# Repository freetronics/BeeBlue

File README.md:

Freetronics Bluetooth Module for XBee
=====================================
Copyright 2014 Freetronics Pty Ltd <http://www.freetronics.com.au>  

A Bluetooth module with an XBee footprint, so that it can be inserted
into boards designed to use XBee modules and give them Bluetooth
capability instead.

More information is available at:

  http://www.freetronics.com.au/beeblue

INSTALLATION
------------
The design is saved as an EAGLE project. EAGLE PCB design software is
available from www.cadsoftusa.com free for non-commercial use. To use
this project download it and place the directory containing these files
into the "eagle" directory on your computer. Then open EAGLE and
navigate to the project.

DISTRIBUTION
------------
The specific terms of distribution of this project are governed by the
license referenced below.

LICENSE
-------
Licensed under the TAPR Open Hardware License (www.tapr.org/OHL).
The "license" folder within this repository also contains a copy of
this license in plain text format.

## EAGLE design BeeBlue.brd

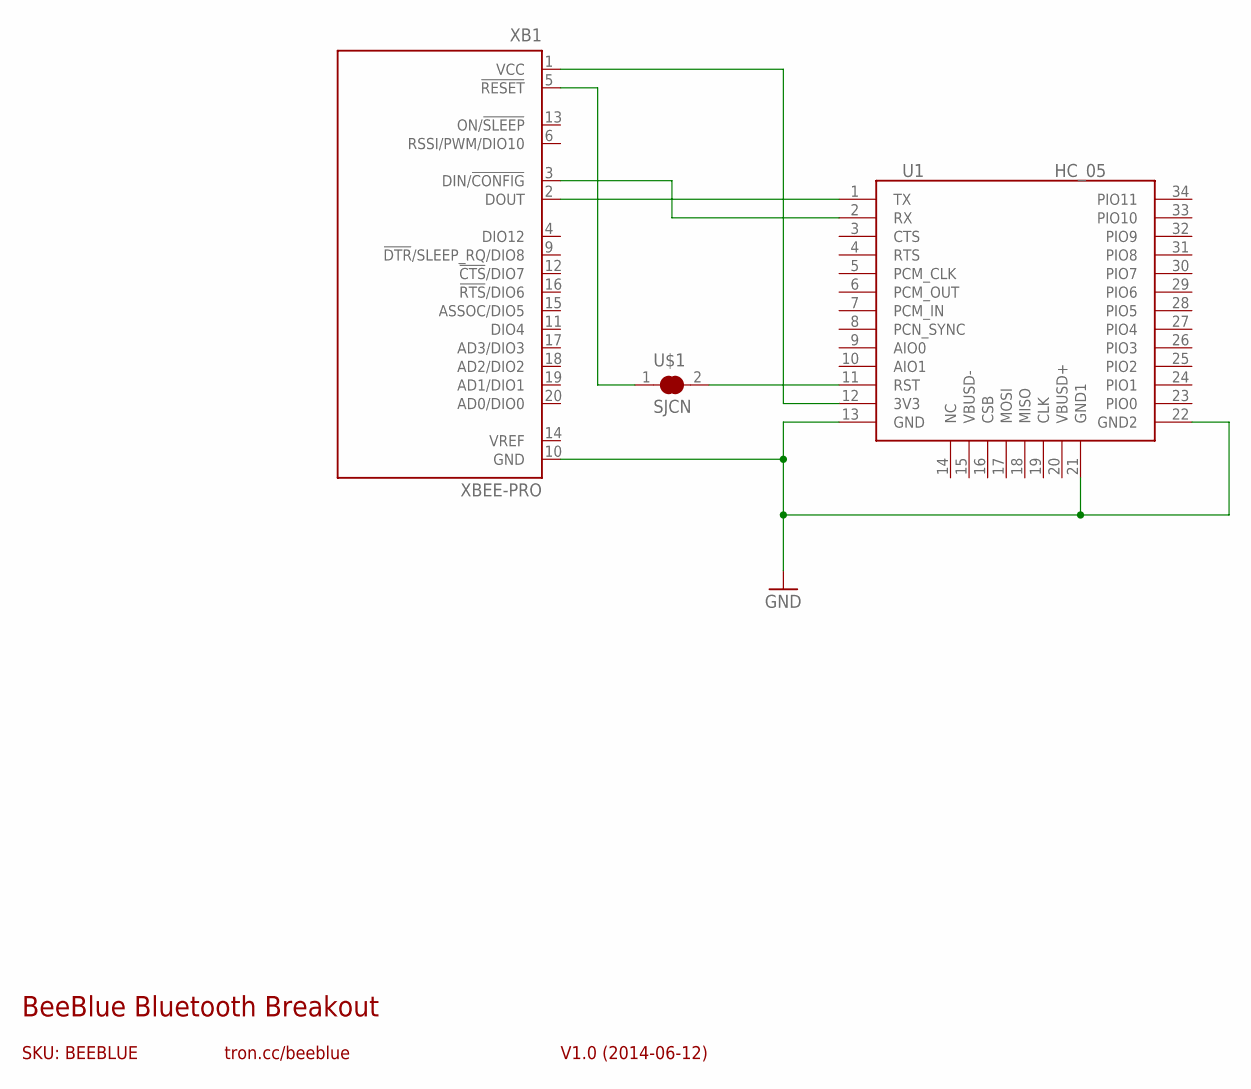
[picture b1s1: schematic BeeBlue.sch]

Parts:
U1: HC_05; BLUETOOTH_SMD
U$1: SJCN; SJC
XB1: XBEE-PRO

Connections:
GND: U1.13 (GND), U1.21 (GND1), U1.22 (GND2), XB1.10 (GND)
unnamed: U1.1 (TX), XB1.2 (DOUT)
unnamed: U1.2 (RX), XB1.3 (DIN/!CONFIG)
unnamed: U1.12 (3V3), XB1.1 (VCC)
unnamed: U1.11 (RST), U$1.2
unnamed: U$1.1, XB1.5 (!RESET)

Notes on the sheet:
SKU: BEEBLUE
BeeBlue Bluetooth Breakout
V1.0 (2014-06-12)
tron.cc/beeblue

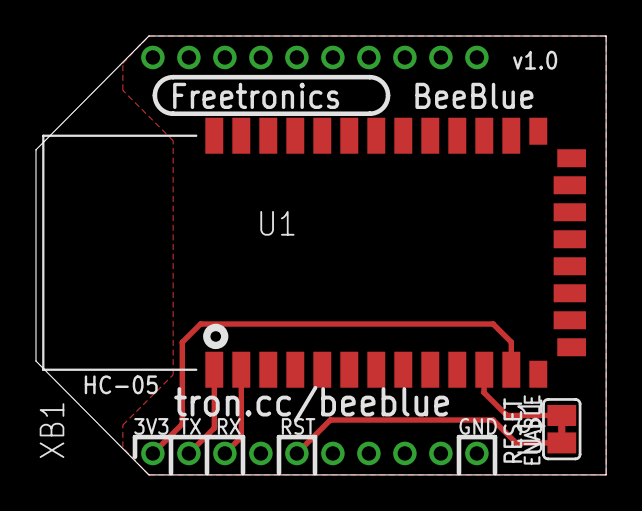
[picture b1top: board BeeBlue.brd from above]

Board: 2 copper layers, 31.7 x 24.4 mm, 3 parts (0 on the bottom side), 6 nets.

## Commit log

2014-06-12 Initial project import
2014-06-12 Added jumper for setting command mode
2018-03-27 Added README and licence

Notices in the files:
BeeBlue.brd:
(c)2014 Freetronics Pty Ltd
Hardware License tapr.org/OHL
